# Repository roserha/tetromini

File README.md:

# Tetromini - STM Edition (In active development)

This is a refactor of the old Nordic/Zephyr version of the project for the STM32F405/freeRTOS pipeline that is archived in `dev`!

## About
Tetromini is a portable console based on an Adafruit Feather STM32F405 Express running a custom firmware inside freeRTOS that plays a fan-made version of a falling-block puzzle game!

The project consists of multiple parts. As of writing, the firmware that controls the console itself and the game inside the firmware have a working version!

Future developments may want to explore things such as:
- [ ] Game over screens
- [ ] High score tracking (?)
- [ ] A custom enclosure shaped like a T-Block Tetromino

## Features
- Sprite-based rendering
- 4 directional inputs (move left, move right, soft drop, hard drop)
- Clockwise and counterclockwise rotation
- Dynamic gravity and boosted score based on level
- Combo points per consecutive line clears
- Pseudorandomly chosen pieces
- Dropped pieces and 4 different line clear sound effects
- Multi-channel soundtrack played via synthesized notes with custom notes system
- Multithreaded parallel execution

## Schematics, PCB and BOM
The below KiCad schematic is based on Rev 1, running on a breadboard, and set to run on a PCB under Rev 1a. (last updated Oct 28th 2026)

Bill Of Materials for Rev 1a (last updated Oct 28th 2026):
| Reference                                                       | Description                             | MPN      | DigiKey PN                 | Manufacturer |
|-----------------------------------------------------------------|-----------------------------------------|----------|----------------------------|--------------|
| U1                                                              | Feather STM32F405 Express               | 4382     | 1528-4382-ND               | Adafruit     |
| DS1                                                             | Generic 2.42in SSD1309 OLED SPI Display | --       | --                         | HiLetgo      |
| DS2                                                             | I2S Audio Breakout                      | 14809    | 1568-14809-ND              | Sparkfun     |
| DOWN1,LEFT1,RIGHT1,ROT_LEFT1,ROT_RIGHT1,UP1,START_BTN,POWER_BTN | Push button switch, generic, two pins   | MJTP1234 | 679-2442-ND                | APEM Inc.    |
| C1,C2,C3,C4,C5,C6,C7,C8                                         | 100nF Capacitor                         | C320C104K5R5TA | 399-4264-ND          | KEMET        |
| C9                                                              | 100UF Capacitor                         | 16ZLH100MEFC5X11 | 1189-1148-ND       | Rubycon      |
| R1,R2,R5,R6,R9,R10,R13,R14                                      | 10kOhm Resistor                         | ROX05SJ10K | A142728CT-ND             | TE Connectivity Passive Product |
| R3,R4,R7,R8,R11,R12,R15,R16                                     | 100kOhm Resistor                        | WK202070A1003J2200 | 749-WK202070A1003J2200CT-ND | Vishay |
| SW1                                                             | SPDT Switch                             | SS12SDP2 | 360-2133-ND                | NKK Switches |
| --                                                              | 8ohm 700MW Speaker                      | CMS-181325-078L100B-67 | 2223-CMS-181325-078L100B-67-ND | Same Sky |
| --                                                              | Lithium Battery                         | 258      | 1528-1838-ND               | Adafruit     |
| --                                                              | SMD SWD Header for Feather              | 4048     | 1528-2827-ND               | Adafruit     |
| --                                                              | Headers for Feather                     | 2886     | 1528-1560-ND               | Adafruit     |
| --                                                              | Headers for OLED and I2S Breakout       | PPTC071LFBN-RC | S7005-ND             | Sullins Connector Solutions |

## Firmware and Multithreading

The project's firmware is based on FreeRTOS, and is set up by multiple concurrent threads that run in parallel. Their execution and basic behaviours can be seen below:

```mermaid
---
config:
  look: neo
  theme: redux-color
---
sequenceDiagram
    participant App as Main Application
    participant Game as Game Thread
    participant Render as Render Thread
    participant Battery as Battery Level Thread
    participant ButtonISR as Button Interrupts
    participant Audio as Audio Thread
    participant Melody as Melody Thread
    participant Video as Video Thread
    participant Decoder as Decoder Thread
    participant MCU as STM32F405

    MCU->>App: Spawn Main Application inside FreeRTOS

    App->>Render: Spawn thread
    App->>Battery: Spawn thread
    App->>Audio: Spawn thread
    App->>Melody: Spawn thread
    App->>Game: Spawn thread

    Render->>MCU: Initialize OLED via SPI + DMA
    Audio->>MCU: Initialize amp via I2S + DMA

    par Frame Math
        loop Single Frame (every ~33ms)
            Game->>Game: Process inputs from input queue
            Game->>Game: Process logic dependent on Screen State
            Game->>Audio: Send any SFX to play, if appropriate
            Game->>App: Update framebuffer (mutexed)
            Game->>Render: Notify frame is ready to be rendered
            Game->>Game: Sleep for ~33ms
            Render->>MCU: Transmit updated framebuffer to SSD1309 via DMA (mutexed FB + waits on semaphored DMA state)
            Render->>Render: Sleep until transfer finished or timed out
            MCU->>Render: Notify transfer finished
        end
    and Audio
        loop Every 2.6ms
            Audio->>Audio: Await notifications from DMA
            MCU->>Audio: Send buffer half-processed notification
            Audio->>Audio: Prepare first half of next buffer based on channel info in 1.3ms
            Audio->>Audio: Await notifications from DMA
            MCU->>Audio: Send buffer fully-processed notification
            Audio->>Audio: Prepare second half of next buffer based on channel info in 1.3ms
        end
    and Melody
        App->>Melody: Tell Melody Controller to play song
        loop Per Song Command (or perpetually if song chose to be looped)
            Melody->>Melody: If song is looped, loop. Otherwise, sleep until notification to play a new song
            Melody->>Melody: Read stored melody info
            loop Until commands run out
                Melody->>Audio: Send play audio command if note is played
                Melody->>Melody: Wait for however long melody says to wait
            end
        end
    and Battery
        loop Every 5s
            Battery->>MCU: Query battery voltage from ADC 10 times with 750ms in between
            Battery->>Battery: Calculate voltage and percentage
            Battery->>App: Update voltage and percentage
        end
    and Buttons
        loop Continuously
            ButtonISR->>Game: Send input to buffer upon rising or falling edge
        end
    and Video
      loop Every 2s
        par Playback
          Video->>Video: Render first buffer
          loop Until "EOF"
            Video->>App: Update framebuffer with frame (mutexed)
            Video->>Video: Sleep for ~33ms
          end
          Video->>Decoder: Alert first half was rendered
          Video->>Video: Render second buffer
          loop Until "EOF"
            Video->>App: Update framebuffer with frame (mutexed)
            Video->>Video: Sleep for ~33ms
          end
          Video->>Decoder: Alert second half was rendered
        and Decoding
          loop Continuously
            Decoder->>Decoder: Await notifications (change video, new buffer ready)
            MCU->>Decoder: Read video content from flash
            Decoder->>App: INFLATE block into buffer
          end
        end
      end
    end
```

## Controllers
Most of the threads' behaviour (specifically the Melody, Audio and Game Threads) are abstracted away inside of **Controller Classes**. This is the overview of what controllers exist inside those threads, and how they interact with each other. It isn't an expressly formal Design Structure, but the closest I can think is that it's akin to singleton decorators, in a way? Controllers can "engulf" others to add their behaviours to their own, and we only should have one controller instance existing at a time.

```mermaid
---
config:
  look: neo
  theme: redux-color
---
classDiagram
  class GraphicsController {
    +kScreenWidth : uint_fast8_t 
    +kScreenHeight : uint_fast8_t 
    +kFrameBufferSize : uint16_t 
    -_frame_buffer : std::array<uint8_t, kFrameBufferSize>* 
    -_xFrameBufferMutex : SemaphoreHandle_t* 
    +setPixel(const uint_fast8_t x, const uint_fast8_t y, const bool on) : void 
    +unfilledRect(const uint_fast8_t x, const uint_fast8_t y, const uint_fast8_t w, const uint_fast8_t h, const bool on) : void 
    +filledRect(const uint_fast8_t x, const uint_fast8_t y, const uint_fast8_t w, const uint_fast8_t h, const bool on) : void 
  }

  class SpritesController {
    -_sprite_array : std::array<uint8_t, 749> 
    +drawSprite(const uint_fast8_t sprite_id, const uint_fast8_t x, const uint_fast8_t y) : uint8_t 
    +drawBlock(const uint_fast8_t x, const uint_fast8_t y, const Tetromino_t block_type) : bool 
    +drawText(const uint_fast8_t x, const uint_fast8_t y, const char *sentence) : uint_fast8_t 
    +drawNumber(const uint_fast8_t x, const uint_fast8_t y, const int32_t number, const uint_fast8_t base) : uint_fast8_t 
  }

  class TetrominoController {
    +getTetrominoPositions(const uint_fast8_t x, const uint_fast8_t y, const Tetromino_t block_type, const Spin_t spin_state) : void
    +drawTetromino(const uint_fast8_t x, const uint_fast8_t y, const Tetromino_t block_type, const Spin_t spin_state) : void
    +drawPhantomTetromino(const uint_fast8_t x, const uint_fast8_t y, const Tetromino_t block_type, const Spin_t spin_state) : void
  }

  class PlayfieldController {
    -Playfield[22] : uint32_t 
    -Score : uint32_t 
    -Level : uint_fast8_t 
    -TotalLinesCleared : uint32_t 
    -Combo : uint32_t 
    -PieceDropTimeout : uint32_t 
    -seen_pieces : uint_fast8_t 
    -nextPiece : Tetromino_t 
    -currentPiece : Tetromino_t 
    -currentSpinState : Spin_t 
    -pieceXPos : uint_fast8_t 
    -pieceYPos : uint_fast8_t 
    -phantomYPos : uint_fast8_t 
    -stopwatch : int64_t 
    -checkForLineClear : bool 
    -finishedCheck : bool 
    -indexesToShift : std::array<uint_fast8_t, 4> 
    -JLSTZ_Offsets : std::array<int8_t, 40> 
    -I_Offsets : std::array<int8_t, 40> 
    -O_Offsets : std::array<bool, 8> 
    -_graphicsController : GraphicsController* 
    -_spritesController : SpritesController* 
    -_tetrominoController : TetrominoController* 
    -_salt : uint32_t*
    -_audioQueue : QueueHandle_t
    +setBlockState(const uint8_t x, const uint8_t y, const uint8_t block_type) : void 
    +renderPlayfield() : void 
    +renderPlayfieldHeader() : void 
    +pullNewPiece() : Tetromino_t
    +checkForCollision(const Tetromino_t block_type, const Spin_t spin_state, const uint_fast8_t x, const uint_fast8_t y) : bool 
    +rotateCurrentPiece(const bool clockwise) : void 
    +moveCurrentPiece(const bool right) : void 
    +softDropCurrentPiece() : void 
    +hardDropCurrentPiece() : void 
    +setSoftDropStatus(const bool status) : void
    +updatePhantomPiecePosition() : void 
    +initializePlayfield() : void 
    +tickPlayfield(const uint32_t delta_time, const uint32_t elapsed_time) : void 
  }

  class AudioController {
    +playWave(const uint8_t waveId, const uint16_t pitch, const uint16_t time, const uint8_t volume) : void 
    +processAudioCallback(bool secondHalf) : void 
    +sampleToUlValue(const uint32_t waveNumber, const uint32_t note, const uint32_t octave, const uint32_t volume, const uint32_t length) : uint32_t $
    -kChannelNumber : uint32_t $
    -Channels : std::array<SoundChannel_t, kChannelNumber> 
    -lastSample : uint16_t 
    -_audioDMABuffer : std::array<int16_t, 256>*
    -kSineWave : std::array<int16_t, 600> $
    -kAKWF_eguitar_002 : std::array<int16_t, 600> $
    -kAKWF_ebass_061 : std::array<int16_t, 600> $
    -kAKWF_vgame_059 : std::array<int16_t, 600> $
  }

  class MelodyController {
    +playSong(const uint8_t songId, const bool loop) : void 
    +getSongMessage() : uint32_t 
    -currentSong : uint32_t 
    -currentSongMessage : uint32_t 
    -shouldSongLoop : bool 
    -main_song : std::array<uint32_t, 483> $
  }

SpritesController "1" ..> "1" GraphicsController
GraphicsController "1" ..> "1" TetrominoController
PlayfieldController "1" ..> "1" GraphicsController
PlayfieldController "1" ..> "1" SpritesController
PlayfieldController "1" ..> "1" TetrominoController
```

## Sprite Rendering
Given we only have 1MB of flash and 128KB of RAM, the 6x6 px sprites need to take up as little space as possible. Since the OLED display is monochrome, they are stored in binary pixel format.

Given a source bitmap tilemap of all sprites, for each one, a count of their collumns (and therefore their horizontal resolution) is stored, and then each collumn is stored in a byte, with two leftover bits, for a total of 7 bytes per sprite. The actual arrays are programatically calculated and written down via a Python script run at build time.

When rendering sprites, a caret system is used to allow for interchanging and nested text and number rendering by leveraging the column size parameter.

Each sprite, when rendered, is stored in a framebuffer that gets sent via SPI + DMA to the OLED display through a custom SSD1309 driver. Each pixel drawing and render command protects the buffer via a Mutex.

## Melody Playback

Given that a singular second of stored audio would be 96KB given an audio playback of 48kHz and 16-bit amplitude resolution, it is impractical (to put it lightly) to store full scores. As such, given the programmed behaviour of the Audio Task, songs are stored as several "play note" and "sleep" commands calculated from a given MIDI file.

Commands are arranged as follows: a 32-bit word arranged with masks as follows: `0x1F` for note (N), `0xE0` for octave (C), `0xFFF00` for length (L), `0x7F00000` for volume (V), `0x78000000` for waveId (W) for a final word `0b0WWW WVVV VVVV LLLL LLLL LLLL CCCN NNNN`. The most significant bit is restricted to indicate a wait time on stored songs, followed by a 31-bit integer indicating how many milliseconds to sleep before the next command.

This made it such that, for example, the `main_song.mid` file, whose raw uncompressed wave would occupy **3.686MB** for a 38.4s playback, and MIDI file occupies *2.4KB*, takes up around *1.932KB* in flash! It does depend on the arrangement, however, because a 20.5KB piano arrangement MIDI takes up ~25KB. It still beats its theoretical uncompressed size of ~20MB!

## Audio Synthesization

To generate the sound waves for the different instruments, the raw amplitudes of a single wave are stored as 600 16-bit integers spread equidistant across the single wavelength, and a "jump" floating point number is calculated based on the wave's desired pitch and the 48kHz playback. This means each instrument takes up around 1.2KB. Upon playback, we use that number to "jump" across amplitudes during playback to simulate pitch shifting. Each wave has an attack and decay envelope to avoid crackling on consecutive playbacks. The audio system can support up to `kChannelNumber` different waves to be played at the same time. A 256-integer-long buffer is then sent via I2S + Circular DMA to the I2S Breakout, and each half is filled based on ISR routines sent by the DMA coroutine.

## Video Playback

For the Main Menu screen, a 3D animation plays. This would be computationally intensive to generate on the fly, and as such, a video encoding system was devised via a double circular buffer. The video task reads from two buffers of 36 frames each, and whenever one's reading is finished, it alerts the decoding task that that buffer is ready for new frames, and goes onto the next, so on ad infinitum (or as infinitum as a game console can be). Because GameTask initially was the only one that rendered information to the screen, VideoTask and GameTask now take turns having ownership of a DisplayControl mutex, so one task doesn't render over another.

## Video Encoding/Decoding

Given the size of video files and our RAM, it would be impractical to store the entire video in the heap (let alone any task's stack). As such, we store two buffers of decoded output and processing buffers inside the decoder itself. Video frames are encoded to be in the same bit resolution and pixel order as the framebuffer, and groups of 36 (or less for the leftovers) are stored together and DEFLATEd together using ZLIB. For decoding, I utilize [zlib_turbo](https://github.com/bitbank2/zlib_turbo/tree/main) for faster performance, with some modifications for it to fit my firmware's intended behaviour. 72 frames of animation get stored in 6.5KB in flash, compared to the overall 73.74KB that both blocks (comprised of 72 frames) take up.

With Video and Audio available, I hid a little fun easter egg inside of the project! You can read the source code to figure out what music video gets played, but I'm happy to say that its ~6500 frames only take up 479KB of space in flash!

## "Random" Piece Generation
Since RTOSs are to be deterministic machines, true randomness isn't recommended. However, it is wished that games don't look the same across gameplays. As such, a custom pseudorandom number generation system was created in addition to a traditional "bag system" wherein each of the 7 pieces are pulled from a metaphorical "bag" before being reshuffled when all of them are pulled. This bag system ensures that no same piece is ever pulled more than twice in a row.

As soon as gameplay begins, a salt is initialized and incremented by 26489 every frame, and set to wrap at 2147457158. To further randomize initial conditions, a random number of pieces are pulled out and discarded, and two pieces are chosen at random. Whenever it is time to choose a piece at (seemingly) random, this salt is added to 3739 times the current ticks since boot for an internal random variable, and then the salt is incremented by 14929. By this nature, under extremely precise and calculated circumstances, gameplay COULD be fully deterministic, but under normal gameplay, it is seemingly random.

## Debugging
Debugging is achieved live on the board using a Segger J-Link EDU! This project is purely for learning's sake, so yay!

## Disclaimer
Tetris® is a registered trademark of The Tetris Company, LLC. This project is not affiliated with or endorsed by The Tetris Company.

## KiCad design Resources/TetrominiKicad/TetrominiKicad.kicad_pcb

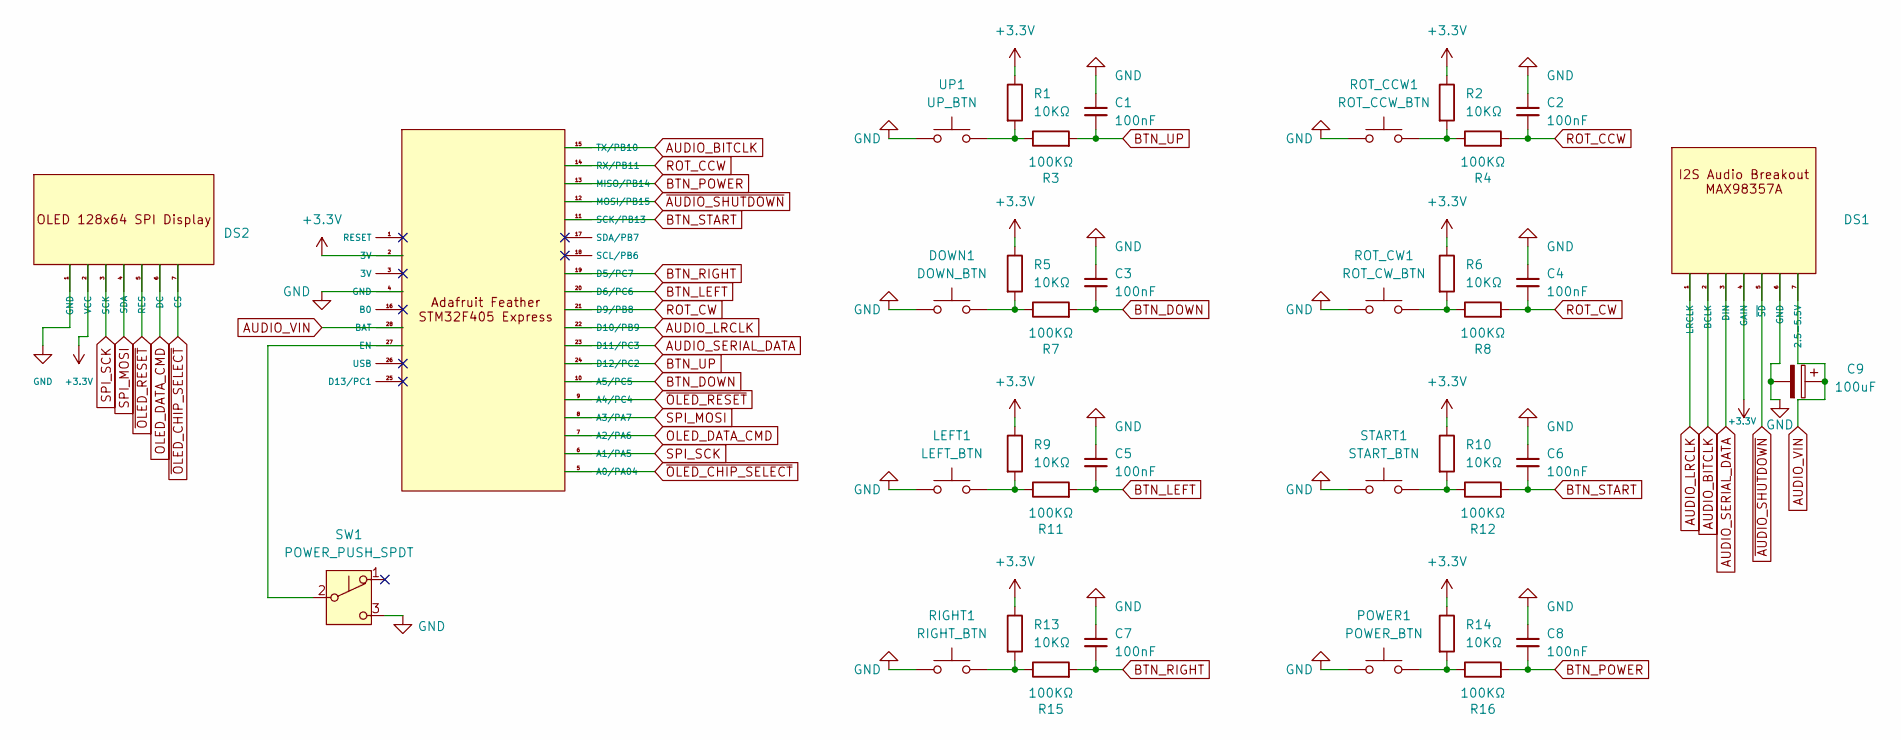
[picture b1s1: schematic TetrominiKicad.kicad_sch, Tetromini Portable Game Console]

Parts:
C1, C2, C3, C4, C5, C6, C7, C8: 100nF; C_Disc_D5.0mm_W2.5mm_P5.00mm
C9: 100uF; CP_Radial_D5.0mm_P2.00mm
DOWN1: DOWN_BTN; SW_PUSH_6mm; MPN MJTP1234; DigiKey_PN 679-2442-ND
DS1: PinSocket_1x07_P2.54mm_Vertical
DS2: PinSocket_1x07_P2.54mm_Vertical; MPN --; DigiKey_PN --
LEFT1: LEFT_BTN; SW_PUSH_6mm; MPN MJTP1234; DigiKey_PN 679-2442-ND
POWER1: POWER_BTN; SW_PUSH_6mm
R1, R2, R5, R6, R9, R10, R13, R14: 10KΩ; R_Axial_DIN0207_L6.3mm_D2.5mm_P7.62mm_Horizontal
R3, R4, R7, R8, R11, R12, R15, R16: 100KΩ; R_Axial_DIN0207_L6.3mm_D2.5mm_P7.62mm_Horizontal
RIGHT1: RIGHT_BTN; SW_PUSH_6mm; MPN MJTP1234; DigiKey_PN 679-2442-ND
ROT_CCW1: ROT_CCW_BTN; SW_PUSH_6mm; MPN MJTP1234; DigiKey_PN 679-2442-ND
ROT_CW1: ROT_CW_BTN; SW_PUSH_6mm; MPN MJTP1234; DigiKey_PN 679-2442-ND
START1: START_BTN; SW_PUSH_6mm
SW1: POWER_PUSH_SPDT; PinHeader_1x03_P2.54mm_Vertical
U1: Adafruit_Feather
UP1: UP_BTN; SW_PUSH_6mm; MPN MJTP1234; DigiKey_PN 679-2442-ND

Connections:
+3.3V: DS1.4 (GAIN), DS2.2 (VCC), R1.1, R2.1, R5.1, R6.1, R9.1, R10.1, R13.1, R14.1, U1.2 (3V)
AUDIO_BITCLK: DS1.2 (BCLK), U1.15 (TX/PB10)
AUDIO_LRCLK: DS1.1 (LRCLK), U1.22 (D10/PB9)
AUDIO_SERIAL_DATA: DS1.3 (DIN), U1.23 (D11/PC3)
AUDIO_VIN: C9.1, DS1.7 (2.5-5.5V), U1.28 (BAT)
BTN_DOWN: C3.2, R7.2, U1.10 (A5/PC5)
BTN_LEFT: C5.2, R11.2, U1.20 (D6/PC6)
BTN_POWER: C8.2, R16.2, U1.13 (MISO/PB14)
BTN_RIGHT: C7.2, R15.2, U1.19 (D5/PC7)
BTN_START: C6.2, R12.2, U1.11 (SCK/PB13)
BTN_UP: C1.2, R3.2, U1.24 (D12/PC2)
GND: C1.1, C2.1, C3.1, C4.1, C5.1, C6.1, C7.1, C8.1, C9.2, DOWN1.1, DS1.6 (GND), DS2.1 (GND), LEFT1.1, POWER1.1, RIGHT1.1, ROT_CCW1.1, ROT_CW1.1, START1.1, SW1.3 (C), U1.4 (GND), UP1.1
unnamed: DOWN1.2, R5.2, R7.1
unnamed: LEFT1.2, R9.2, R11.1
unnamed: POWER1.2, R14.2, R16.1
unnamed: R1.2, R3.1, UP1.2
unnamed: R2.2, R4.1, ROT_CCW1.2
unnamed: R6.2, R8.1, ROT_CW1.2
unnamed: R10.2, R12.1, START1.2
unnamed: R13.2, R15.1, RIGHT1.2
unnamed: SW1.2 (B), U1.27 (EN)
OLED_DATA_CMD: DS2.6 (DC), U1.7 (A2/PA6)
ROT_CCW: C2.2, R4.2, U1.14 (RX/PB11)
ROT_CW: C4.2, R8.2, U1.21 (D9/PB8)
SPI_MOSI: DS2.4 (SDA), U1.8 (A3/PA7)
SPI_SCK: DS2.3 (SCK), U1.6 (A1/PA5)
~AUDIO_SHUTDOWN: DS1.5 (~SD), U1.12 (MOSI/PB15)
~OLED_CHIP_SELECT: DS2.7 (CS), U1.5 (A0/PA04)
~OLED_RESET: DS2.5 (RES), U1.9 (A4/PC4)

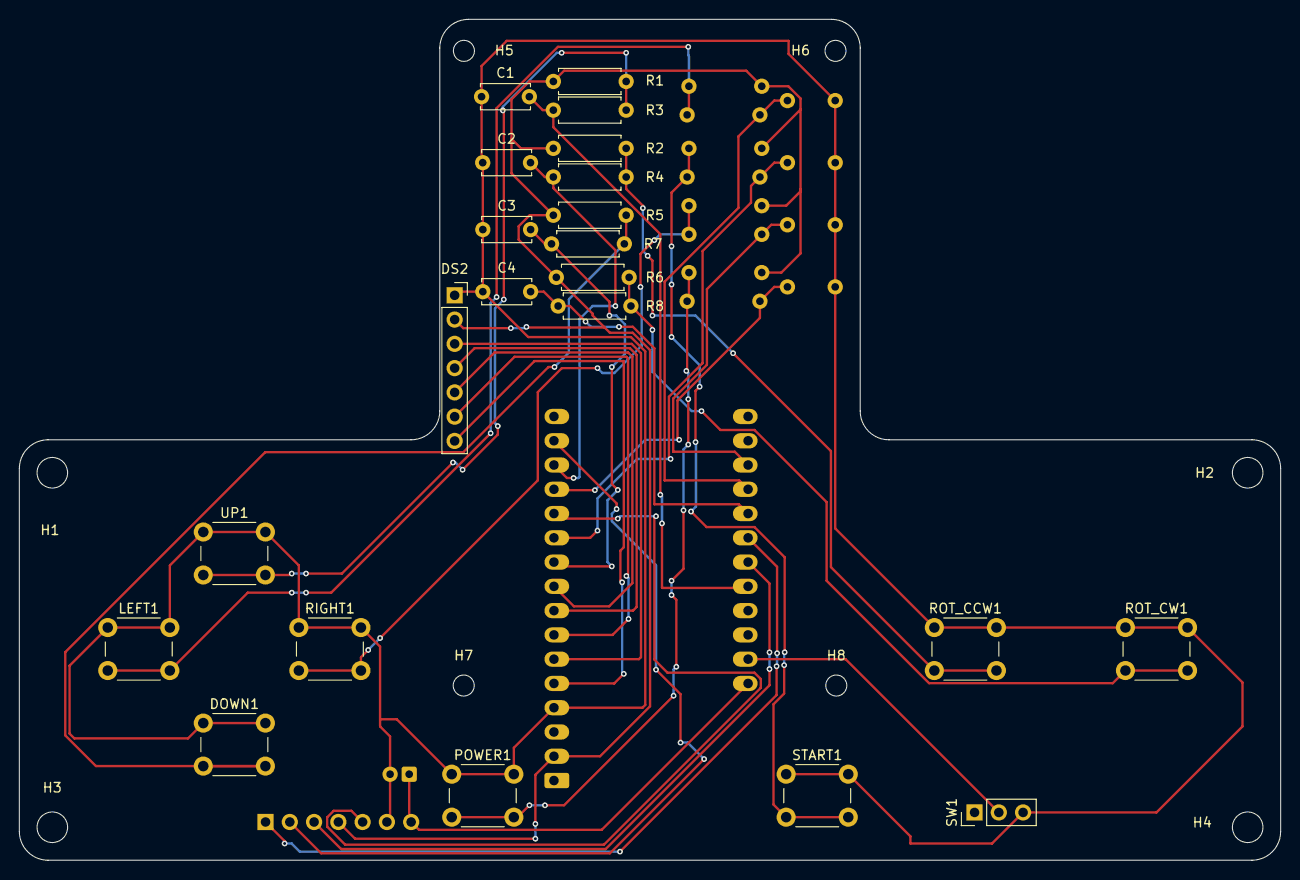
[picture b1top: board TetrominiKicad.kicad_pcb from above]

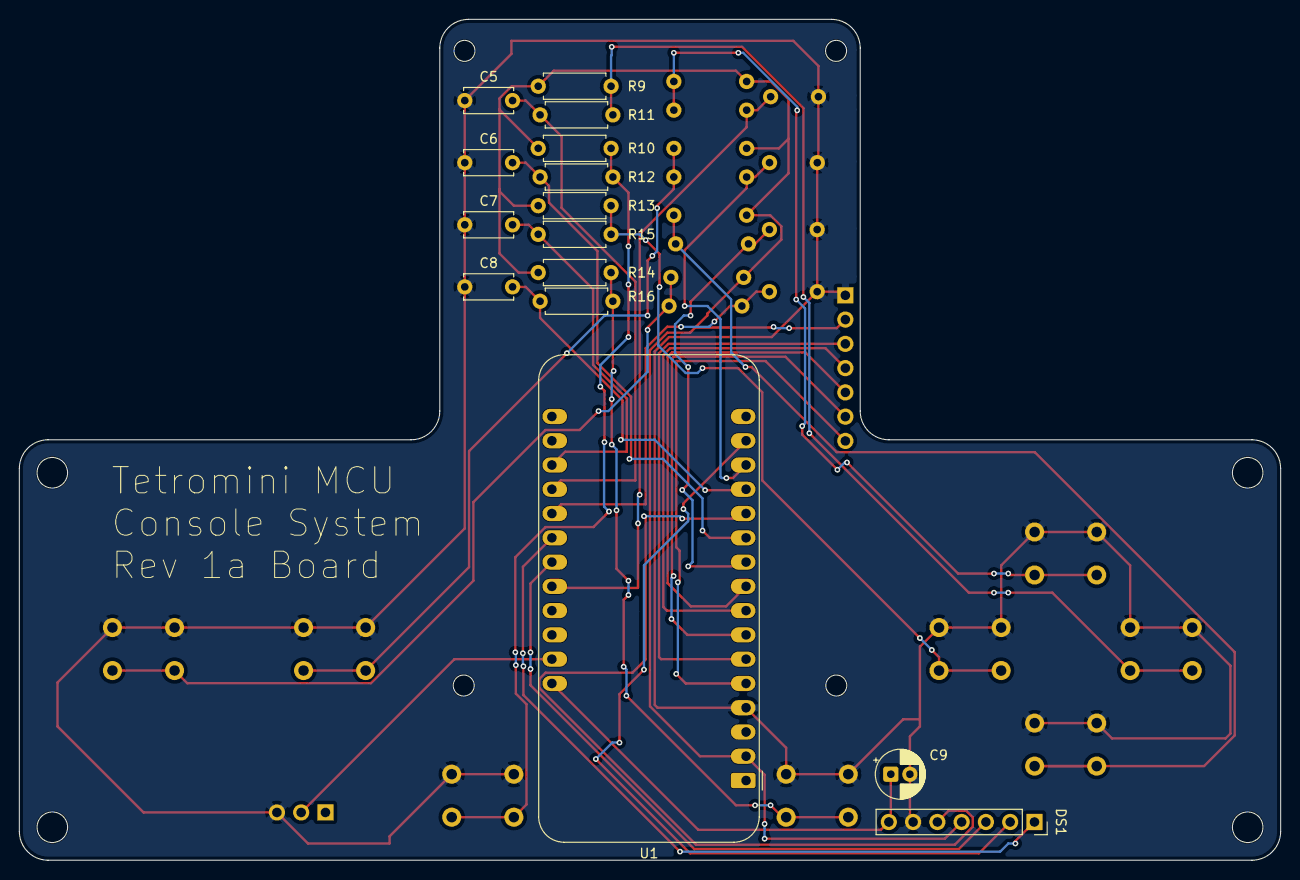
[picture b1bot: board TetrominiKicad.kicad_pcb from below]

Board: 2 copper layers, 132.0 x 88.0 mm, 45 parts (15 on the bottom side), 29 nets.

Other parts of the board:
H1, H2, H3, H4: MountingHole_3.2mm_M3
H5, H6, H7, H8: MountingHole_2.2mm_M2

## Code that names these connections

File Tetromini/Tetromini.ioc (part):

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Mcu.Name=STM32F405RGTx
Mcu.Package=LQFP64
Mcu.UserName=STM32F405RGTx
PA13.Mode=Serial_Wire
PA13.Signal=SYS_JTMS-SWDIO
PA14.Mode=Serial_Wire
PA14.Signal=SYS_JTCK-SWCLK
PA3.GPIOParameters=GPIO_Label
PA3.GPIO_Label=VBAT_SENSE
PA3.Signal=ADCx_IN3
PA4.GPIOParameters=PinState,GPIO_Label
PA4.GPIO_Label=OLED_CS
PA4.PinState=GPIO_PIN_SET
PA4.Signal=GPIO_Output
PA5.Mode=TX_Only_Simplex_Unidirect_Master
PA5.Signal=SPI1_SCK
PA6.GPIOParameters=PinState,GPIO_Label
PA6.GPIO_Label=OLED_DC
PA6.PinState=GPIO_PIN_SET
PA6.Signal=GPIO_Output
PA7.Mode=TX_Only_Simplex_Unidirect_Master
PA7.Signal=SPI1_MOSI
PB10.Mode=Half_Duplex_Master
PB10.Signal=I2S2_CK
PB11.GPIOParameters=GPIO_PuPd,GPIO_Label,GPIO_ModeDefaultEXTI
PB11.GPIO_Label=BTN_CCW
PB11.GPIO_ModeDefaultEXTI=GPIO_MODE_IT_RISING_FALLING
PB11.GPIO_PuPd=GPIO_PULLUP
PB11.Signal=GPXTI11
PB13.GPIOParameters=GPIO_PuPd,GPIO_Label,GPIO_ModeDefaultEXTI
PB13.GPIO_Label=BTN_START
PB13.GPIO_ModeDefaultEXTI=GPIO_MODE_IT_RISING_FALLING
PB13.GPIO_PuPd=GPIO_PULLUP
PB13.Signal=GPXTI13
PB14.GPIOParameters=GPIO_PuPd,GPIO_Label,GPIO_ModeDefaultEXTI
PB14.GPIO_Label=BTN_POWER
PB14.GPIO_ModeDefaultEXTI=GPIO_MODE_IT_RISING_FALLING
PB14.GPIO_PuPd=GPIO_PULLUP
PB14.Signal=GPXTI14
PB15.GPIOParameters=GPIO_Label
PB15.GPIO_Label=AUDIO_SHUTDOWN
PB15.Signal=GPIO_Output
PB8.GPIOParameters=GPIO_PuPd,GPIO_Label,GPIO_ModeDefaultEXTI
PB8.GPIO_Label=BTN_CW
PB8.GPIO_ModeDefaultEXTI=GPIO_MODE_IT_RISING_FALLING
PB8.GPIO_PuPd=GPIO_PULLUP
PB8.Signal=GPXTI8
PB9.Mode=Half_Duplex_Master
PB9.Signal=I2S2_WS
PC1.GPIOParameters=GPIO_Label
PC1.GPIO_Label=Blinky
PC1.Signal=GPIO_Output
PC2.GPIOParameters=GPIO_PuPd,GPIO_Label,GPIO_ModeDefaultEXTI
PC2.GPIO_Label=BTN_UP
PC2.GPIO_ModeDefaultEXTI=GPIO_MODE_IT_RISING_FALLING
PC2.GPIO_PuPd=GPIO_PULLUP
PC2.Signal=GPXTI2
PC3.Mode=Half_Duplex_Master
PC3.Signal=I2S2_SD
PC4.GPIOParameters=GPIO_Label
PC4.GPIO_Label=OLED_RESET
PC4.Signal=GPIO_Output
PC5.GPIOParameters=GPIO_PuPd,GPIO_Label,GPIO_ModeDefaultEXTI
PC5.GPIO_Label=BTN_DOWN
PC5.GPIO_ModeDefaultEXTI=GPIO_MODE_IT_RISING_FALLING
PC5.GPIO_PuPd=GPIO_PULLUP
PC5.Signal=GPXTI5
PC6.GPIOParameters=GPIO_PuPd,GPIO_Label,GPIO_ModeDefaultEXTI
PC6.GPIO_Label=BTN_LEFT
PC6.GPIO_ModeDefaultEXTI=GPIO_MODE_IT_RISING_FALLING
PC6.GPIO_PuPd=GPIO_PULLUP
PC6.Signal=GPXTI6
PC7.GPIOParameters=GPIO_PuPd,GPIO_Label,GPIO_ModeDefaultEXTI
PC7.GPIO_Label=BTN_RIGHT
PC7.GPIO_ModeDefaultEXTI=GPIO_MODE_IT_RISING_FALLING
PC7.GPIO_PuPd=GPIO_PULLUP
PC7.Signal=GPXTI7
PH0-OSC_IN.Mode=HSE-External-Oscillator
PH0-OSC_IN.Signal=RCC_OSC_IN
PH1-OSC_OUT.Mode=HSE-External-Oscillator
PH1-OSC_OUT.Signal=RCC_OSC_OUT
RCC.HSE_VALUE=12000000
RCC.SYSCLKFreq_VALUE=168000000
RCC.SYSCLKSource=RCC_SYSCLKSOURCE_PLLCLK
board=custom
